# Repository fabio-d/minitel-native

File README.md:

# minitel-native

Software and hardware tools to run native programs on the
[Minitel](https://en.wikipedia.org/wiki/Minitel).

<p align="center">

<br />

<br />

</p>

## Usage instructions

* Insert the [ROM emulation board](rom-emulation/) in the Minitel's ROM socket.
* Load one or more ROMs, directly through the Minitel's serial port (or over a
  wireless network), using
  [`rom-emulator-cli.py`](rom-emulation/firmware/scripts/rom-emulator-cli.py).
* Select the one to be started at power-on, on the Minitel itself.
* Try out the [example programs](examples/) and [create your own](lib/)!

## Supported Minitel models

This project targets Minitel models based on 8052-compatible CPUs and the
EF9345/TS9347 video chips. The following models are currently supported:

* RTIC Minitel 1 (NFZ 330)
* Philips Minitel 2 (NFZ 400, NMS 6202/19B and NMS 6202/19W)
* HOBS Viewdata Banking Terminal (NMS 6302/00B)
* Telic-Alcatel Minitel 12 (722039 M)

## License

Software in this repository is licensed under the
[GNU Lesser General Public License v3](COPYING-SW.txt).
Hardware design files in this repository are licensed under the
[CERN Open Hardware Licence v2, Weakly Reciprocal](COPYING-HW.txt).

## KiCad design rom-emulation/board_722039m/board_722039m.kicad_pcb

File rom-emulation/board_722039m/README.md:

# Adapter board for 722039 M Minitels

This board supports the following Minitel models:

* Telic-Alcatel Minitel 12 (722039 M)

**Note**: the battery[^1]-powered RAM chip is optional. If omitted (or if no
batteries are installed), the Minitel will lose its address book and messages at
every boot.

[^1]: The Minitel 12's battery slot is located under the display (two 1.5V AA)
and easily accessible without disassembling. See page 4 of the
[Minitel 12 manual](https://www.minitel-alcatel.fr/documents/M12_1988/M12%20%20Mode%20d'emploi.pdf).

## Bill of materials

* Surface mounted (included in the production files for PCB fabrication):
  * **U3**: SN74CB3T16211 Bus Switch TSSOP
    ([datasheet](https://www.ti.com/lit/gpn/SN74CB3T16211),
    [LCSC/JLCPCB](https://jlcpcb.com/partdetail/C2653275)).
  * **Y1**: 12 MHz Crystal
    ([LCSC/JLCPCB](https://jlcpcb.com/partdetail/C9002)).
  * **D1**: 1N5819 Schottky diode SOD-323
    ([LCSC/JLCPCB](https://jlcpcb.com/partdetail/C191023)).
  * **C1, C3**: 1 &micro;F Capacitor 0603
    ([LCSC/JLCPCB](https://jlcpcb.com/partdetail/C15849)).
  * **C2, C6**: 100 nF Capacitor 0603
    ([LCSC/JLCPCB](https://jlcpcb.com/partdetail/C14663)).
  * **C4, C5**: 30 pF Capacitor 0402
    ([LCSC/JLCPCB](https://jlcpcb.com/partdetail/C1570)).
  * **R1, R2, R6**: 8.2 k&ohm; Resistor 0603
    ([LCSC/JLCPCB](https://jlcpcb.com/partdetail/C25981)).
  * **R3, R4, R5**: 22 k&ohm; Resistor 0402
    ([LCSC/JLCPCB](https://jlcpcb.com/partdetail/C25768)).
* Others (to be purchased and assembled separately):
  * Raspberry Pico 2 or Raspberry Pico 2 W
    ([RP2350 datasheet](https://datasheets.raspberrypi.com/rp2350/rp2350-datasheet.pdf),
    [Pico 2 datasheet](https://datasheets.raspberrypi.com/pico/pico-2-datasheet.pdf),
    [Pico 2 W datasheet](https://datasheets.raspberrypi.com/picow/pico-2-w-datasheet.pdf)).
  * P8032AH microcontroller in DIP package
    ([AliExpress](https://www.aliexpress.com/item/1005003690963062.html)).
  * 40-pin DIP socket
    ([AliExpress](https://www.aliexpress.com/item/1005006256010892.html)).
  * Two 20-pin female headers
    ([AliExpress](https://www.aliexpress.com/item/32854239374.html)).
  * One 32-pin male header
    ([AliExpress](https://www.aliexpress.com/item/1005006034877497.html)), or a
    longer one cut accordingly.
* And, optionally, for battery-powered RAM support:
  * 23LCV512 SPI RAM in PDIP package
    ([datasheet](https://ww1.microchip.com/downloads/en/devicedoc/25157a.pdf)).
  * 8-pin DIP socket
    ([AliExpress](https://www.aliexpress.com/item/1005006256010892.html)).

## Assembling the board

Solder the headers as shown in the pictures and populate the sockets with the
corresponding chips.

Use solder to close bridges JP1 and JP2 in one of the ways shown below,
depending on the clock configuration of the Minitel's original CPU board:

<table>
  <tr>
    <td align="center">
      <br />
      Position 1-1:<br />
      Use external clock
    </td>
    <td align="center">
      <br />
      Position 3-3:<br />
      Use on-board clock
    </td>
  </tr>
</table>

Choose position 3-3 only if the original CPU board has a crystal on it (see
[example pictures](https://commons.wikimedia.org/wiki/File:Crystal_Packages.jpg)
for what it looks like - note that it might be horizontal rather than vertical
too). If no crystal is present in the original CPU board, choose position 1-1.

## Installation

> [!TIP]
> Some of the original design documents for this Minitel have been published at
> [this page](https://www.minitel-alcatel.fr/M12.html). The "M12 Description
> Technique 1988" file has a picture of the internal boards at page 18 and the
> original schematics at the end. The "Hardware M12" document has revised
> schematics that seem to better match the actual circuits in my Minitel.

Installation is straightforward: pull the original CPU board out of the main
board and replace it with the new board.

## Schematic

## Pinout

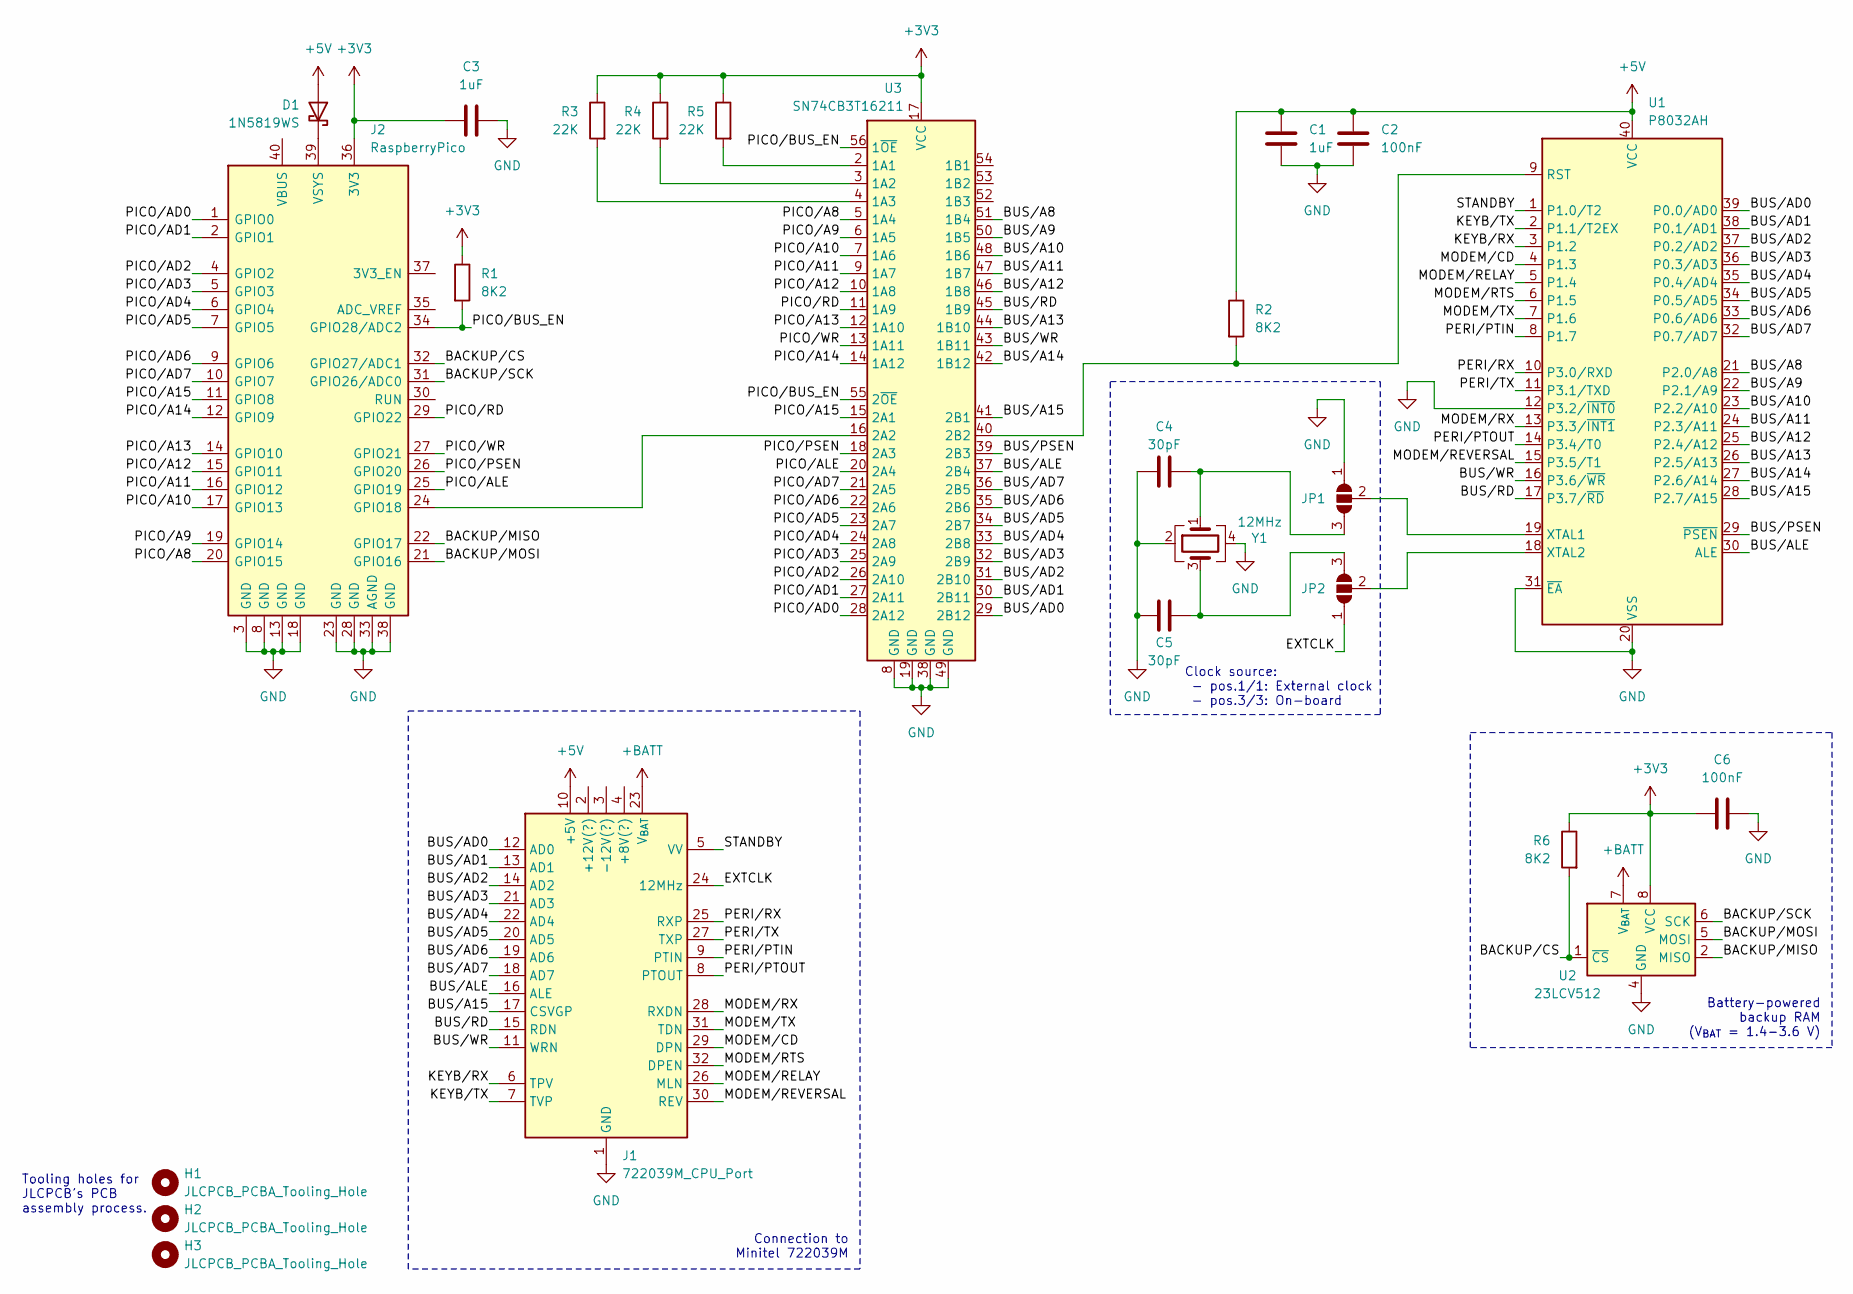
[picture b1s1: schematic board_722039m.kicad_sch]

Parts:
C1, C3: 1uF; C_0603_1608Metric
C2, C6: 100nF; C_0603_1608Metric
C4, C5: 30pF; C_0402_1005Metric
D1: 1N5819WS; D_SOD-323
H1, H2, H3: JLCPCB_PCBA_Tooling_Hole; ToolingHole_1.152mm
J1: 722039M_CPU_Port; PinHeader_1x32_P2.54mm_Vertical
J2: RaspberryPico; RaspberryPi_Pico_Common_THT
JP1, JP2: SolderJumper_3_Open; SolderJumper-3_P1.3mm_Open_RoundedPad1.0x1.5mm
R1, R2, R6: 8K2; R_0603_1608Metric
R3, R4, R5: 22K; R_0402_1005Metric
U1: P8032AH; DIP-40_W15.24mm_Socket
U2: 23LCV512; DIP-8_W7.62mm_Socket
U3: SN74CB3T16211; TSSOP-56_6.1x14mm_P0.5mm
Y1: 12MHz; Crystal_SMD_3225-4Pin_3.2x2.5mm

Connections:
+3V3: C3.1, C6.1, J2.36 (3V3), R1.1, R3.1, R4.1, R5.1, R6.1, U2.8 (VCC), U3.17 (VCC)
+5V: C1.1, C2.1, D1.2 (A), J1.10 (+5V), R2.1, U1.40 (VCC)
+BATT: J1.23 (V_{BAT}), U2.7 (V_{BAT})
/BACKUP/CS: J2.32 (GPIO27/ADC1), R6.2, U2.1 (~CS)
/BACKUP/MISO: J2.22 (GPIO17), U2.2 (MISO)
/BACKUP/MOSI: J2.21 (GPIO16), U2.5 (MOSI)
/BACKUP/SCK: J2.31 (GPIO26/ADC0), U2.6 (SCK)
/BUS/A8: U1.21 (P2.0/A8), U3.51 (1B4)
/BUS/A9: U1.22 (P2.1/A9), U3.50 (1B5)
/BUS/A10: U1.23 (P2.2/A10), U3.48 (1B6)
/BUS/A11: U1.24 (P2.3/A11), U3.47 (1B7)
/BUS/A12: U1.25 (P2.4/A12), U3.46 (1B8)
/BUS/A13: U1.26 (P2.5/A13), U3.44 (1B10)
/BUS/A14: U1.27 (P2.6/A14), U3.42 (1B12)
/BUS/A15: J1.17 (CSVGP), U1.28 (P2.7/A15), U3.41 (2B1)
/BUS/AD0: J1.12 (AD0), U1.39 (P0.0/AD0), U3.29 (2B12)
/BUS/AD1: J1.13 (AD1), U1.38 (P0.1/AD1), U3.30 (2B11)
/BUS/AD2: J1.14 (AD2), U1.37 (P0.2/AD2), U3.31 (2B10)
/BUS/AD3: J1.21 (AD3), U1.36 (P0.3/AD3), U3.32 (2B9)
/BUS/AD4: J1.22 (AD4), U1.35 (P0.4/AD4), U3.33 (2B8)
/BUS/AD5: J1.20 (AD5), U1.34 (P0.5/AD5), U3.34 (2B7)
/BUS/AD6: J1.19 (AD6), U1.33 (P0.6/AD6), U3.35 (2B6)
/BUS/AD7: J1.18 (AD7), U1.32 (P0.7/AD7), U3.36 (2B5)
/BUS/ALE: J1.16 (ALE), U1.30 (ALE), U3.37 (2B4)
/BUS/PSEN: U1.29 (~PSEN), U3.39 (2B3)
/BUS/RD: J1.15 (RDN), U1.17 (P3.7/~RD), U3.45 (1B9)
/BUS/WR: J1.11 (WRN), U1.16 (P3.6/~WR), U3.43 (1B11)
/EXTCLK: J1.24 (12MHz), JP2.1 (A)
/KEYB/RX: J1.6 (TPV), U1.3 (P1.2)
/KEYB/TX: J1.7 (TVP), U1.2 (P1.1/T2EX)
/MODEM/CD: J1.29 (DPN), U1.4 (P1.3)
/MODEM/RELAY: J1.26 (MLN), U1.5 (P1.4)
/MODEM/REVERSAL: J1.30 (REV), U1.15 (P3.5/T1)
/MODEM/RTS: J1.32 (DPEN), U1.6 (P1.5)
/MODEM/RX: J1.28 (RXDN), U1.13 (P3.3/~INT1)
/MODEM/TX: J1.31 (TDN), U1.7 (P1.6)
/PERI/PTIN: J1.9 (PTIN), U1.8 (P1.7)
/PERI/PTOUT: J1.8 (PTOUT), U1.14 (P3.4/T0)
/PERI/RX: J1.25 (RXP), U1.10 (P3.0/RXD)
/PERI/TX: J1.27 (TXP), U1.11 (P3.1/TXD)
/PICO/A8: J2.20 (GPIO15), U3.5 (1A4)
/PICO/A9: J2.19 (GPIO14), U3.6 (1A5)
/PICO/A10: J2.17 (GPIO13), U3.7 (1A6)
/PICO/A11: J2.16 (GPIO12), U3.9 (1A7)
/PICO/A12: J2.15 (GPIO11), U3.10 (1A8)
/PICO/A13: J2.14 (GPIO10), U3.12 (1A10)
/PICO/A14: J2.12 (GPIO9), U3.14 (1A12)
/PICO/A15: J2.11 (GPIO8), U3.15 (2A1)
/PICO/AD0: J2.1 (GPIO0), U3.28 (2A12)
/PICO/AD1: J2.2 (GPIO1), U3.27 (2A11)
/PICO/AD2: J2.4 (GPIO2), U3.26 (2A10)
/PICO/AD3: J2.5 (GPIO3), U3.25 (2A9)
/PICO/AD4: J2.6 (GPIO4), U3.24 (2A8)
/PICO/AD5: J2.7 (GPIO5), U3.23 (2A7)
/PICO/AD6: J2.9 (GPIO6), U3.22 (2A6)
/PICO/AD7: J2.10 (GPIO7), U3.21 (2A5)
/PICO/ALE: J2.25 (GPIO19), U3.20 (2A4)
/PICO/BUS_EN: J2.34 (GPIO28/ADC2), R1.2, U3.55 (2~OE), U3.56 (1~OE)
/PICO/PSEN: J2.26 (GPIO20), U3.18 (2A3)
/PICO/RD: J2.29 (GPIO22), U3.11 (1A9)
/PICO/WR: J2.27 (GPIO21), U3.13 (1A11)
/STANDBY: J1.5 (VV), U1.1 (P1.0/T2)
GND: C1.2, C2.2, C3.2, C4.1, C5.1, C6.2, J1.1 (GND), J2.3 (GND), J2.8 (GND), J2.13 (GND), J2.18 (GND), J2.23 (GND), J2.28 (GND), J2.33 (AGND), J2.38 (GND), JP1.1 (A), U1.12 (P3.2/~INT0), U1.20 (VSS), U1.31 (~EA), U2.4 (GND), U3.8 (GND), U3.19 (GND), U3.38 (GND), U3.49 (GND), Y1.2, Y1.4
unnamed: D1.1 (K), J2.39 (VSYS)
unnamed: J2.24 (GPIO18), U3.16 (2A2)
unnamed: C4.2, JP1.3 (B), Y1.1
unnamed: JP1.2 (C), U1.19 (XTAL1)
unnamed: C5.2, JP2.3 (B), Y1.3
unnamed: JP2.2 (C), U1.18 (XTAL2)
unnamed: R2.2, U1.9 (RST), U3.40 (2B2)
unnamed: R5.2, U3.2 (1A1)
unnamed: R4.2, U3.3 (1A2)
unnamed: R3.2, U3.4 (1A3)

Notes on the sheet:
Battery-powered backup RAM (V_{BAT} = 1.4-3.6 V)
Clock source: - pos.1/1: External clock - pos.3/3: On-board
Tooling holes for JLCPCB's PCB assembly process.
Connection to Minitel 722039M

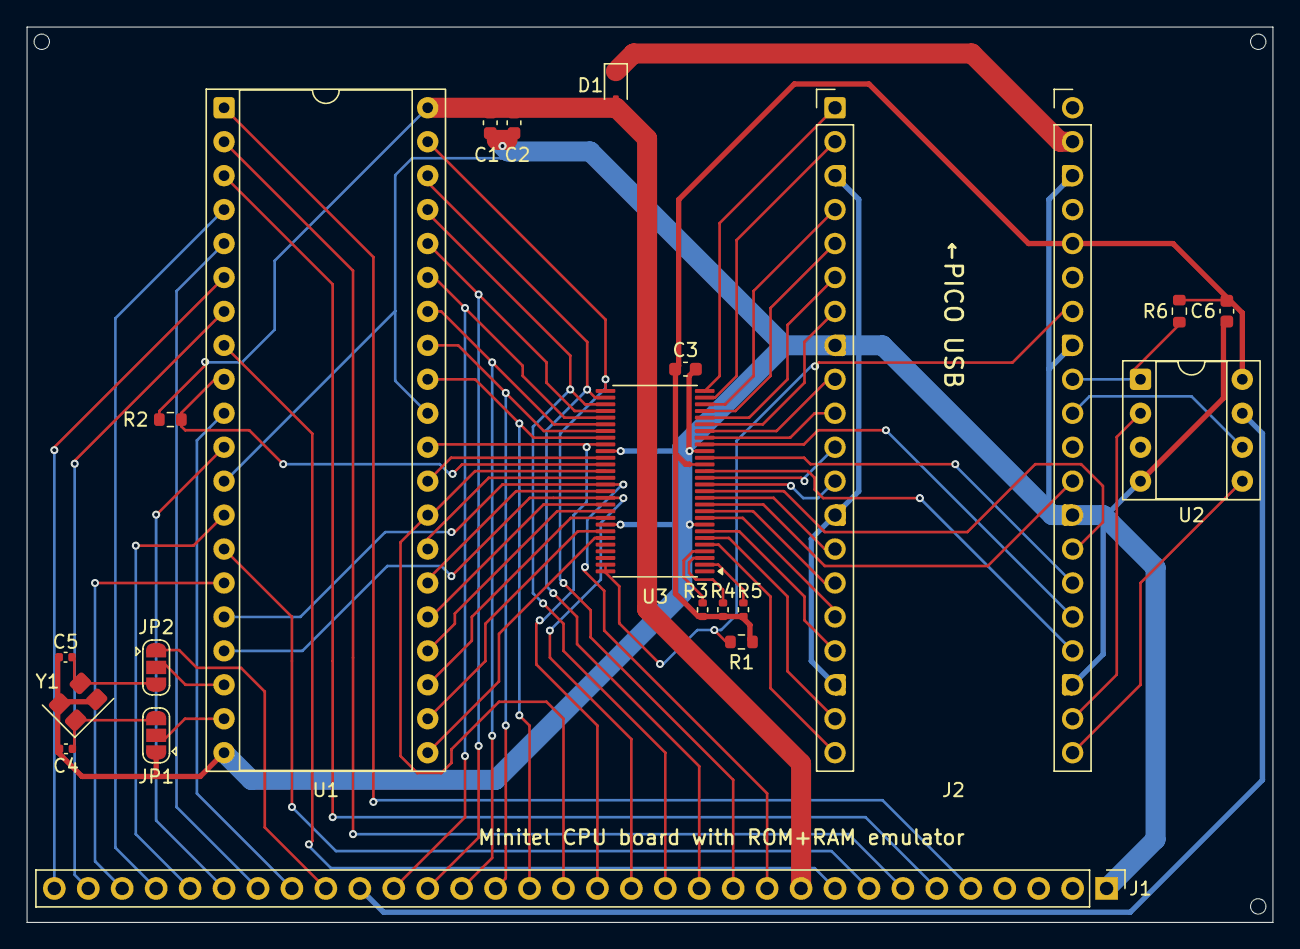
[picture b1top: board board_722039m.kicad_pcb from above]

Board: 2 copper layers, 93.2 x 67.0 mm, 24 parts (0 on the bottom side), 73 nets.

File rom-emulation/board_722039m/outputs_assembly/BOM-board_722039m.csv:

Comment,Designator,Footprint,LCSC,Quantity
100nF,"C2,C6",C_0603_1608Metric,C14663,2
30pF,"C4,C5",C_0402_1005Metric,C1570,2
1uF,"C1,C3",C_0603_1608Metric,C15849,2
1N5819WS,D1,D_SOD-323,C191023,1
22K,"R3,R4,R5",R_0402_1005Metric,C25768,3
8K2,"R1,R2,R6",R_0603_1608Metric,C25981,3
SN74CB3T16211,U3,TSSOP-56_6.1x14mm_P0.5mm,C2653275,1
12MHz,Y1,Crystal_SMD_3225-4Pin_3.2x2.5mm,C9002,1

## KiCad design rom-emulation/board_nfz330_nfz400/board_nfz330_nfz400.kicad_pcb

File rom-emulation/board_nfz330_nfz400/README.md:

# Adapter board for NFZ 330 and NFZ 400 Minitels

This board supports the following Minitel models:

* RTIC Minitel 1 (NFZ 330)
* Philips Minitel 2 (NFZ 400, NMS 6202/19B and NMS 6202/19W)
* HOBS Viewdata Banking Terminal (NMS 6302/00B)

## Bill of materials

* Surface mounted (included in the production files for PCB fabrication):
  * **U1**: SN74HCT541 Octal Buffer TSSOP
    ([datasheet](https://www.ti.com/lit/gpn/SN74HCT541),
    [LCSC/JLCPCB](https://jlcpcb.com/partdetail/C436096)).
  * **U2, U3**: SN74CB3T3384 Bus Switch TSSOP
    ([datasheet](https://www.ti.com/lit/gpn/SN74CB3T3384),
    [LCSC/JLCPCB](https://jlcpcb.com/partdetail/C139357)).
  * **D1**: 1N5819 Schottky diode SOD-323
    ([LCSC/JLCPCB](https://jlcpcb.com/partdetail/C191023)).
  * **C1, C3**: 1 &micro;F Capacitor 0603
    ([LCSC/JLCPCB](https://jlcpcb.com/partdetail/C15849)).
  * **C2**: 100 nF Capacitor 0603
    ([LCSC/JLCPCB](https://jlcpcb.com/partdetail/C14663)).
  * **R1, R2, R3, R4, R5, R6, R7, R8**: 1.5 k&ohm; Resistor 0402
    ([LCSC/JLCPCB](https://jlcpcb.com/partdetail/C25867)).
  * **R9, R10**: 8.2 k&ohm; Resistor 0603
    ([LCSC/JLCPCB](https://jlcpcb.com/partdetail/C25981)).
* Others (to be purchased and assembled separately):
  * Raspberry Pico 2 or Raspberry Pico 2 W
    ([RP2350 datasheet](https://datasheets.raspberrypi.com/rp2350/rp2350-datasheet.pdf),
    [Pico 2 datasheet](https://datasheets.raspberrypi.com/pico/pico-2-datasheet.pdf),
    [Pico 2 W datasheet](https://datasheets.raspberrypi.com/picow/pico-2-w-datasheet.pdf)).
  * Two 20-pin female headers
    ([AliExpress](https://www.aliexpress.com/item/32854239374.html)).
  * (ROMless NFZ 330 only) One 2-pin male header
    ([AliExpress](https://www.aliexpress.com/item/1005006034877497.html)), or a
    longer one cut accordingly.
  * (NFZ 330 only) Tall female headers (with bendable legs), either one 10-pin
    and one 15-pin or two 15-pin headers
    ([AliExpress](https://www.aliexpress.com/item/1005007077965713.html)), cut
    accordingly.
  * (NFZ 400 only) Round hole headers, either two 20p
    ([AliExpress](https://www.aliexpress.com/item/1005007563971977.html)), or
    one 40p to be cut in half.

## Assembling the board

Solder the headers as shown in the pictures.

The tall headers, which are necessary for the NFZ 330 only, must be bent towards
the side. The remaining excess length of the legs can be trimmed away with a
cutter. The 2-pin header is only for NFZ 330, too.

The round hole headers are only necessary for the NFZ 400.

## Installation

### RTIC Minitel 1 (NFZ 330)

> [!TIP]
> Pictures of this Minitel model can be found at
> [this page](http://hxc2001.free.fr/yaquoidedans/Minitel-RTIC-Minitel9-NFZ330/index.html)
> by HxC2001. The pinout of the ROM slot has been documented
> [in this post](https://forum.system-cfg.com/viewtopic.php?p=243591#p243591).

If the Minitel originally had a ROM board inserted in the ROM slot, simply
replace it with the new board.

If the Minitel did not have a ROM board (i.e. it would normally boot from the
8052's integrated ROM and the external ROM slot was unpopulated), it is
necessary to also drive the CPU's External Access (EA) pin (#30) to GND. This
can be done with the following DIY cable:

Material:
* One 2-pin female header
  ([AliExpress](https://www.aliexpress.com/item/32854239374.html)), or a longer
  one cut accordingly.
* Grabber probe
  ([AliExpress](https://www.aliexpress.com/item/1005006975901107.html)).
* Wire, to be soldered to both pins on the header side and then hot-glued to
  make it stronger. The probe side must be soldered too.

The probe needs to be attached to the resistor on the Minitel's logic board as
shown in the picture. **Explanation**: the logic board's resistor is a pull-up
that would drive EA high, thus selecting the integrated ROM. By connecting it to
GND (exposed on both adapter board's pins, see the [Pinout](#pinout) below), EA
is driven low, thus selecting the external ROM. The reason why this cable is not
needed in Minitels that originally came with external ROMs is that their
resistor was soldered in the factory in a slightly different position, which
makes it act as a pull-down rather than a pull-up.

### Philips Minitel 2 (NFZ 400, NMS 6202/19B and NMS 6202/19W)

> [!TIP]
> The internals of this Minitel model have been extensively documented in the
> [main page](http://hxc2001.free.fr/minitel/index.html) of HxC2001's analysis.
> The pinout of the ROM socket has been documented
> [in this post](https://forum.system-cfg.com/viewtopic.php?p=249020#p249020)
> (the pinout is shown on the right-hand side with the "slot EPROM Minitel"
> label and it is mirrored left/right).

Installation is straightforward: after removing the old ROM, insert the board in
the proper orientation. It takes a moderate amount of force to push the pins
fully inside the socket.

It is probably a good idea to temporarily extract the Minitel's logic board and
perform the operation on a flat rigid surface, to avoid flexing it while
pushing.

### HOBS Viewdata Banking Terminal (NMS 6302/00B)

Remove the whole expansion board that is present in the socket in which the
NFZ 400 would have just a ROM chip. Then, follow the same instructions as the
NFZ 400.

## Schematic

## Pinout

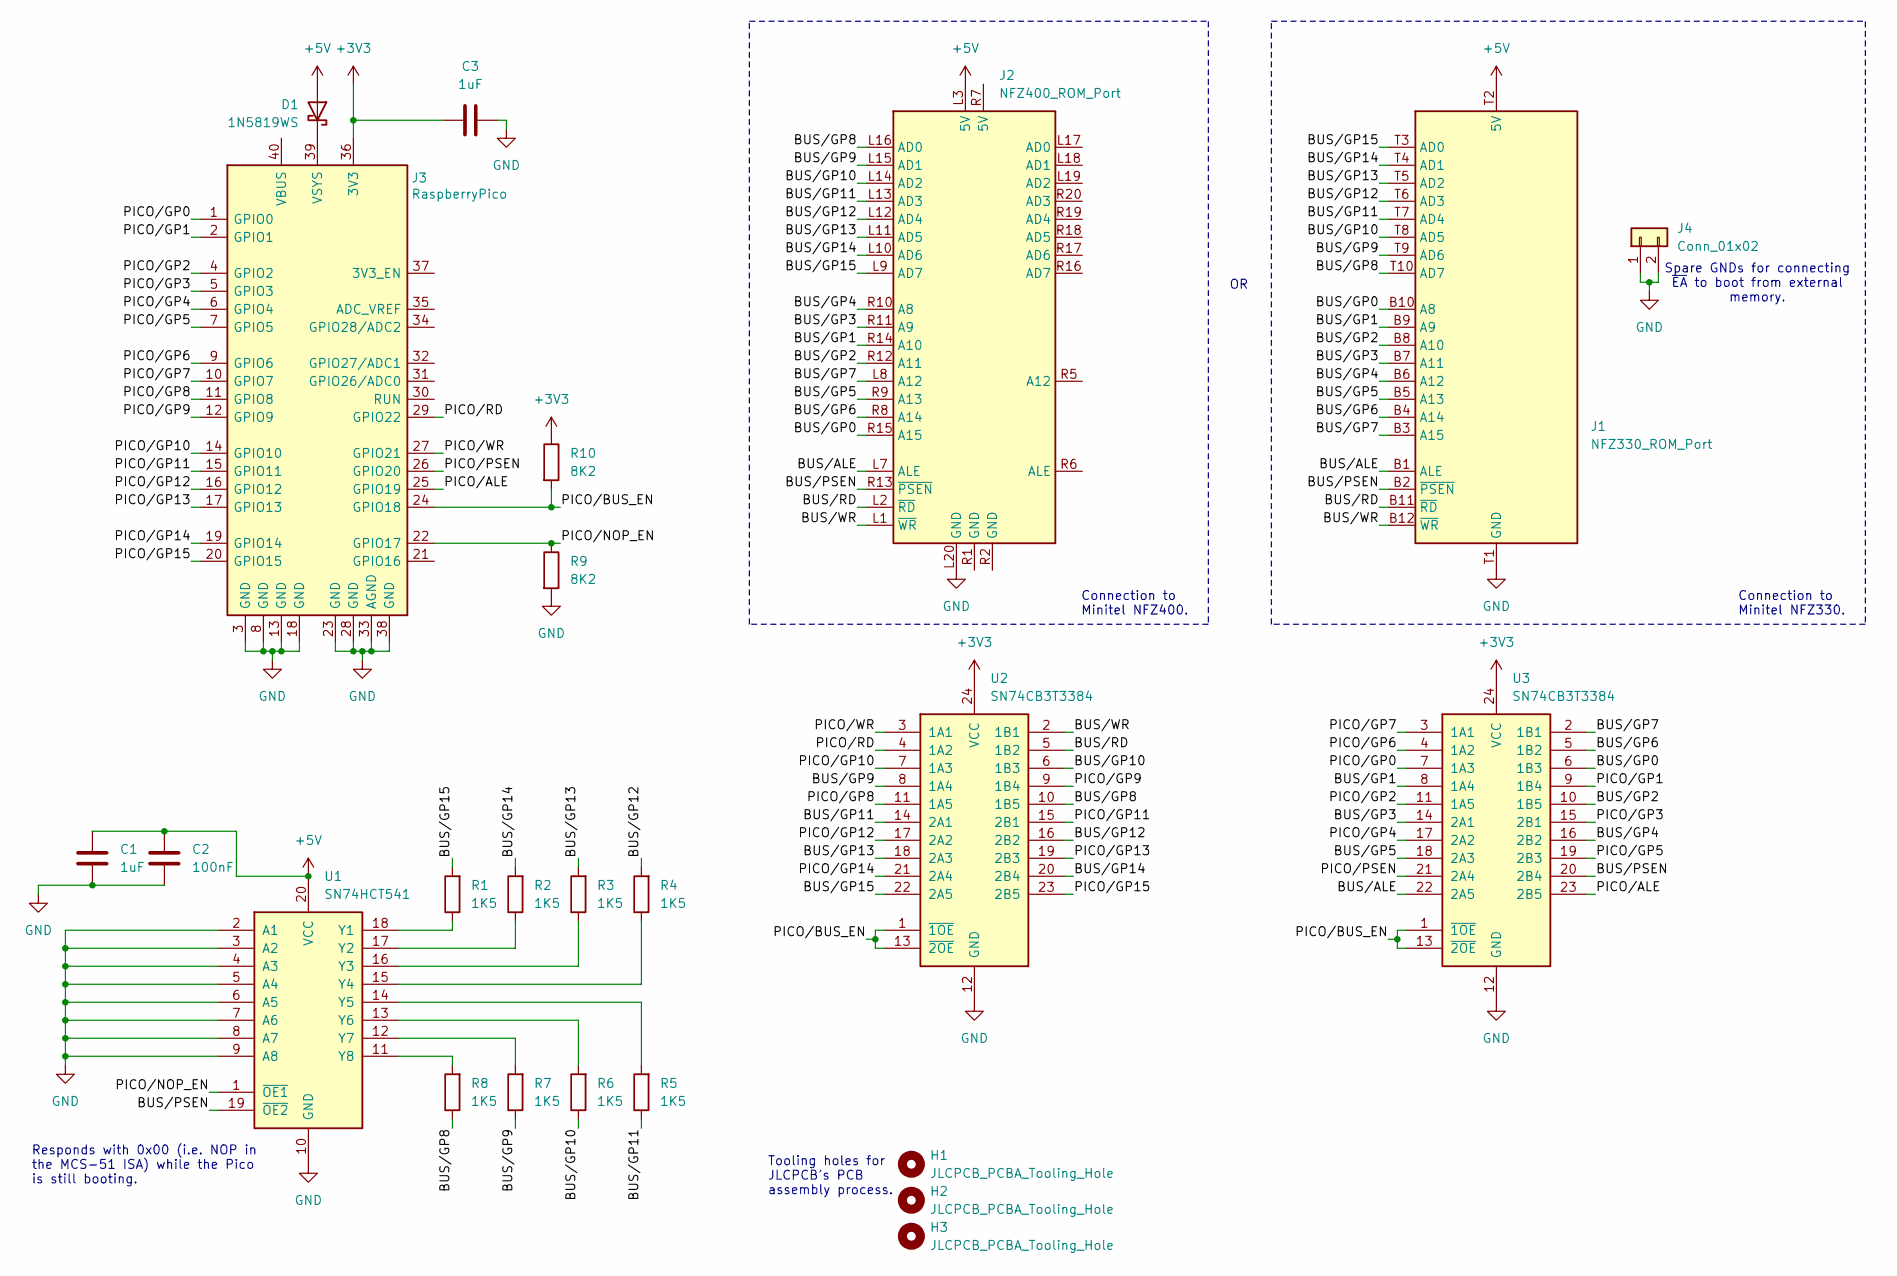
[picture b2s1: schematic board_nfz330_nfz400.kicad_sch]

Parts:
C1, C3: 1uF; C_0603_1608Metric
C2: 100nF; C_0603_1608Metric
D1: 1N5819WS; D_SOD-323
H1, H2, H3: JLCPCB_PCBA_Tooling_Hole; ToolingHole_1.152mm
J1: NFZ330_ROM_Port
J2: NFZ400_ROM_Port
J3: RaspberryPico; RaspberryPi_Pico_Common_THT
J4: Conn_01x02; PinSocket_1x02_P2.54mm_Vertical
R1, R2, R3, R4, R5, R6, R7, R8: 1K5; R_0402_1005Metric
R9, R10: 8K2; R_0603_1608Metric
U1: SN74HCT541; TSSOP-20_4.4x6.5mm_P0.65mm
U2, U3: SN74CB3T3384; TSSOP-24_4.4x7.8mm_P0.65mm

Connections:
+3V3: C3.1, J3.36 (3V3), R10.1, U2.24 (VCC), U3.24 (VCC)
+5V: C1.1, C2.1, D1.2 (A), J1.T2 (5V), J2.L3 (5V), U1.20 (VCC)
/BUS/ALE: J1.B1 (ALE), J2.L7 (ALE), U3.22 (2A5)
/BUS/GP0: J1.B10 (A8), J2.R15 (A15), U3.6 (1B3)
/BUS/GP1: J1.B9 (A9), J2.R14 (A10), U3.8 (1A4)
/BUS/GP2: J1.B8 (A10), J2.R12 (A11), U3.10 (1B5)
/BUS/GP3: J1.B7 (A11), J2.R11 (A9), U3.14 (2A1)
/BUS/GP4: J1.B6 (A12), J2.R10 (A8), U3.16 (2B2)
/BUS/GP5: J1.B5 (A13), J2.R9 (A13), U3.18 (2A3)
/BUS/GP6: J1.B4 (A14), J2.R8 (A14), U3.5 (1B2)
/BUS/GP7: J1.B3 (A15), J2.L8 (A12), U3.2 (1B1)
/BUS/GP8: J1.T10 (AD7), J2.L16 (AD0), R8.1, U2.10 (1B5)
/BUS/GP9: J1.T9 (AD6), J2.L15 (AD1), R7.1, U2.8 (1A4)
/BUS/GP10: J1.T8 (AD5), J2.L14 (AD2), R6.1, U2.6 (1B3)
/BUS/GP11: J1.T7 (AD4), J2.L13 (AD3), R5.1, U2.14 (2A1)
/BUS/GP12: J1.T6 (AD3), J2.L12 (AD4), R4.2, U2.16 (2B2)
/BUS/GP13: J1.T5 (AD2), J2.L11 (AD5), R3.2, U2.18 (2A3)
/BUS/GP14: J1.T4 (AD1), J2.L10 (AD6), R2.2, U2.20 (2B4)
/BUS/GP15: J1.T3 (AD0), J2.L9 (AD7), R1.2, U2.22 (2A5)
/BUS/PSEN: J1.B2 (~PSEN), J2.R13 (~PSEN), U1.19 (~OE2), U3.20 (2B4)
/BUS/RD: J1.B11 (~RD), J2.L2 (~RD), U2.5 (1B2)
/BUS/WR: J1.B12 (~WR), J2.L1 (~WR), U2.2 (1B1)
/PICO/ALE: J3.25 (GPIO19), U3.23 (2B5)
/PICO/BUS_EN: J3.24 (GPIO18), R10.2, U2.1 (~1OE), U2.13 (~2OE), U3.1 (~1OE), U3.13 (~2OE)
/PICO/GP0: J3.1 (GPIO0), U3.7 (1A3)
/PICO/GP1: J3.2 (GPIO1), U3.9 (1B4)
/PICO/GP2: J3.4 (GPIO2), U3.11 (1A5)
/PICO/GP3: J3.5 (GPIO3), U3.15 (2B1)
/PICO/GP4: J3.6 (GPIO4), U3.17 (2A2)
/PICO/GP5: J3.7 (GPIO5), U3.19 (2B3)
/PICO/GP6: J3.9 (GPIO6), U3.4 (1A2)
/PICO/GP7: J3.10 (GPIO7), U3.3 (1A1)
/PICO/GP8: J3.11 (GPIO8), U2.11 (1A5)
/PICO/GP9: J3.12 (GPIO9), U2.9 (1B4)
/PICO/GP10: J3.14 (GPIO10), U2.7 (1A3)
/PICO/GP11: J3.15 (GPIO11), U2.15 (2B1)
/PICO/GP12: J3.16 (GPIO12), U2.17 (2A2)
/PICO/GP13: J3.17 (GPIO13), U2.19 (2B3)
/PICO/GP14: J3.19 (GPIO14), U2.21 (2A4)
/PICO/GP15: J3.20 (GPIO15), U2.23 (2B5)
/PICO/NOP_EN: J3.22 (GPIO17), R9.1, U1.1 (~OE1)
/PICO/PSEN: J3.26 (GPIO20), U3.21 (2A4)
/PICO/RD: J3.29 (GPIO22), U2.4 (1A2)
/PICO/WR: J3.27 (GPIO21), U2.3 (1A1)
GND: C1.2, C2.2, C3.2, J1.T1 (GND), J2.L20 (GND), J3.3 (GND), J3.8 (GND), J3.13 (GND), J3.18 (GND), J3.23 (GND), J3.28 (GND), J3.33 (AGND), J3.38 (GND), J4.1, J4.2, R9.2, U1.2 (A1), U1.3 (A2), U1.4 (A3), U1.5 (A4), U1.6 (A5), U1.7 (A6), U1.8 (A7), U1.9 (A8), U1.10 (GND), U2.12 (GND), U3.12 (GND)
unnamed: D1.1 (K), J3.39 (VSYS)
unnamed: R1.1, U1.18 (Y1)
unnamed: R2.1, U1.17 (Y2)
unnamed: R3.1, U1.16 (Y3)
unnamed: R4.1, U1.15 (Y4)
unnamed: R5.2, U1.14 (Y5)
unnamed: R6.2, U1.13 (Y6)
unnamed: R7.2, U1.12 (Y7)
unnamed: R8.2, U1.11 (Y8)

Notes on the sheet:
Tooling holes for JLCPCB's PCB assembly process.
Connection to Minitel NFZ330.
Responds with 0x00 (i.e. NOP in the MCS-51 ISA) while the Pico is still booting.
Spare GNDs for connecting ~{EA} to boot from external memory.
Connection to Minitel NFZ400.

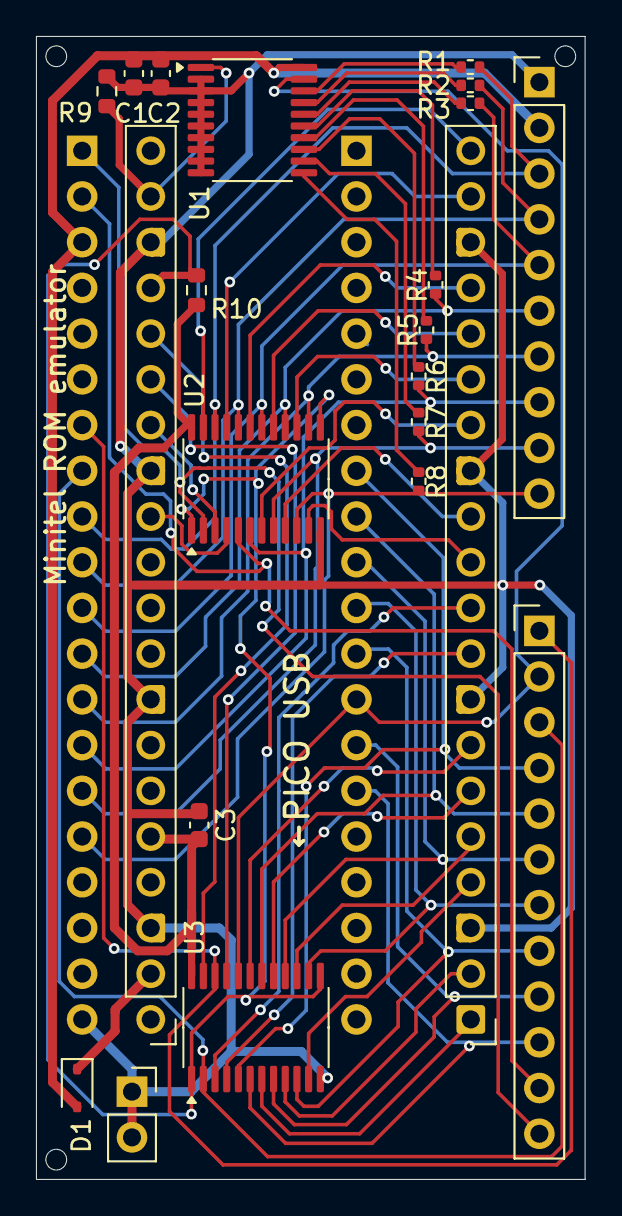
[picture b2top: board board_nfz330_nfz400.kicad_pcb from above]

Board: 2 copper layers, 30.5 x 63.5 mm, 24 parts (1 on the bottom side), 54 nets.

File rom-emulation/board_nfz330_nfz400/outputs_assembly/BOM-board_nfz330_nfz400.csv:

Comment,Designator,Footprint,LCSC,Quantity
SN74CB3T3384,"U2,U3",TSSOP-24_4.4x7.8mm_P0.65mm,C139357,2
100nF,C2,C_0603_1608Metric,C14663,1
1uF,"C1,C3",C_0603_1608Metric,C15849,2
1N5819WS,D1,D_SOD-323,C191023,1
1K5,"R1,R2,R3,R4,R5,R6,R7,R8",R_0402_1005Metric,C25867,8
8K2,"R10,R9",R_0603_1608Metric,C25981,2
SN74HCT541,U1,TSSOP-20_4.4x6.5mm_P0.65mm,C436096,1

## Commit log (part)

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2025-10-04 Initial commit with README and licenses
2025-10-04 ROM emulation program for Pico 2 and Pico 2 W
2025-10-04 Make the SVG diagrams readable with dark themes too
2025-10-04 Add helper libraries and hello_world example program
2025-10-04 Add program that displays arbitrary images using custom fonts
2025-10-04 Describe generic Do-It-Yourself adapter board
2025-10-04 Store up to 16 different ROMs and let the user select one at boot
2025-10-04 Add more details to the main README
2025-10-04 Support for switching back from serving a ROM to just NOPs
2025-10-04 Store/replace ROMs over client protocol
2025-10-04 Tunnel the client protocol over the Minitel's serial port too
    This option must be selected from the Minitel's interactive menu
2025-10-04 Listen for commands over serial port
    Only "ping" is implemented at the moment.
2025-10-04 Add "interactive" mode, that only boots when explicitly told to
    In this mode, the Pico is partitioned:
    - Partition A: contains the Pico program (*).
    - Partition B: contains the alternate Pico program (*).
    - Partition DATA: contains the final Minitel ROM to be
    launched.
    The Pico program embeds a trampoline ROM (not to be confused
2025-10-04 Trace the addresses that are being fetched from the ROM
2025-10-04 Modify startup sequence to get to clear the screen more quickly
2025-10-04 Refresh the menu in response to ROM slot contents being modified
2025-10-04 Hardware design files for the NFZ330/NFZ400 ROM emulation board
2025-10-04 Add program that displays a stream of mosaic images from the serial port
2025-10-05 Fix some typos
2025-10-05 Improve comments in the examples
2025-10-12 Connect to wireless network on Pico 2 W (interactive mode only)
    The wireless credentials can be configured via client protocol
2025-10-12 Add client protocol command to erase a ROM slot
2025-10-12 Accept client protocol over TCP too
    This makes it possible to load new ROMs wirelessly. The other
    methods (serial port and USB) still work.
2025-10-12 Support for reflashing the Pico itself over client protocol
2025-11-01 Add missing else branch
2025-11-01 Reset registers to their reset values in the trampoline
    Without this, the nfz330's stock ROM runs with a wrong baud rate.
2025-11-01 Assign output value through a dedicated state machine
    This has the following advantages:
    - The direction state machines do not have to be interrupted
    - Only one write is necessary from the CPU side
    - The CPU can just send the value, rather than pre-encoded PIO
    instructions
2025-11-01 Optionally emulate RAM too
    When this option is enabled, a high value on A15 activates
    the emulated RAM. This is currently hardcoded.
2025-11-01 Serve the ROM through a DMA chain instead of using core 1
    In addition to freeing up core 1, we no longer need to reserve
    dedicated RAM banks to serving the ROM.
2025-11-01 Make control pins remappable
2025-11-01 Move latching state machine to a separate PIO block
    To free up space in the current PIO block, that will be used in the
    next commits for other programs.
2025-11-01 Proper board installation method for the nfz400
2025-11-01 Rename romemu module to mememu in preparation for emulating RAM too
2025-11-08 Fix two comments
2025-11-08 Properly set 0x00 as the initial output value
    Assigning rxf_putget before the state machine has been initialized
    did not actually set the intended value.
2025-11-08 Better wording in help message
2025-11-08 Updated compatibility list
2025-12-14 Initial firmware support for board_722039m
2025-12-14 Library support for the 722039 M model
2025-12-14 Hardware design files for the 722039 M emulation board
2025-12-14 Fix issue in PIO configuration
    The (no longer necessary) sm_config_set_set_pins call was
    corrupting a control register. See also:
    https://forums.raspberrypi.com/viewtopic.php?p=2123214#p2123214
2026-01-17 Add helper function to reload timers 0 and 1 in mode 1 without losing ticks
    Unlike the previous approach, which lost the ticks that occurred
    before executing the interrupt routine, the now one does not result
    in lost ticks.
    Thanks to this, the hello_world's board periodic task could be
    moved to timer 1 instead of timer 2. Other native programs will be
    updated in the next commits to use timer 1 for the board periodic
2026-01-17 Add support for the Minitel 12 keyboard in other native programs
2026-01-31 Rename board_key_to_name to keyboard_key_to_name
2026-01-31 Optimize 722039m keyboard scanning
2026-01-31 Video stream speed improvements
2026-01-31 Add keyboard_key_is_pressed to quickly test one specific key
2026-01-31 The Minitel 12 is now fully supported
2026-01-31 Optimize nfz400 keyboard scanning
2026-01-31 Implement rounding in timer calculations
    This makes it possible to actually reach 115200 baud on the nfz400
    without workarounds.
2026-01-31 Add menu and triple buffering to the video stream example
2026-01-31 Add hello world picture of the 722039m too
